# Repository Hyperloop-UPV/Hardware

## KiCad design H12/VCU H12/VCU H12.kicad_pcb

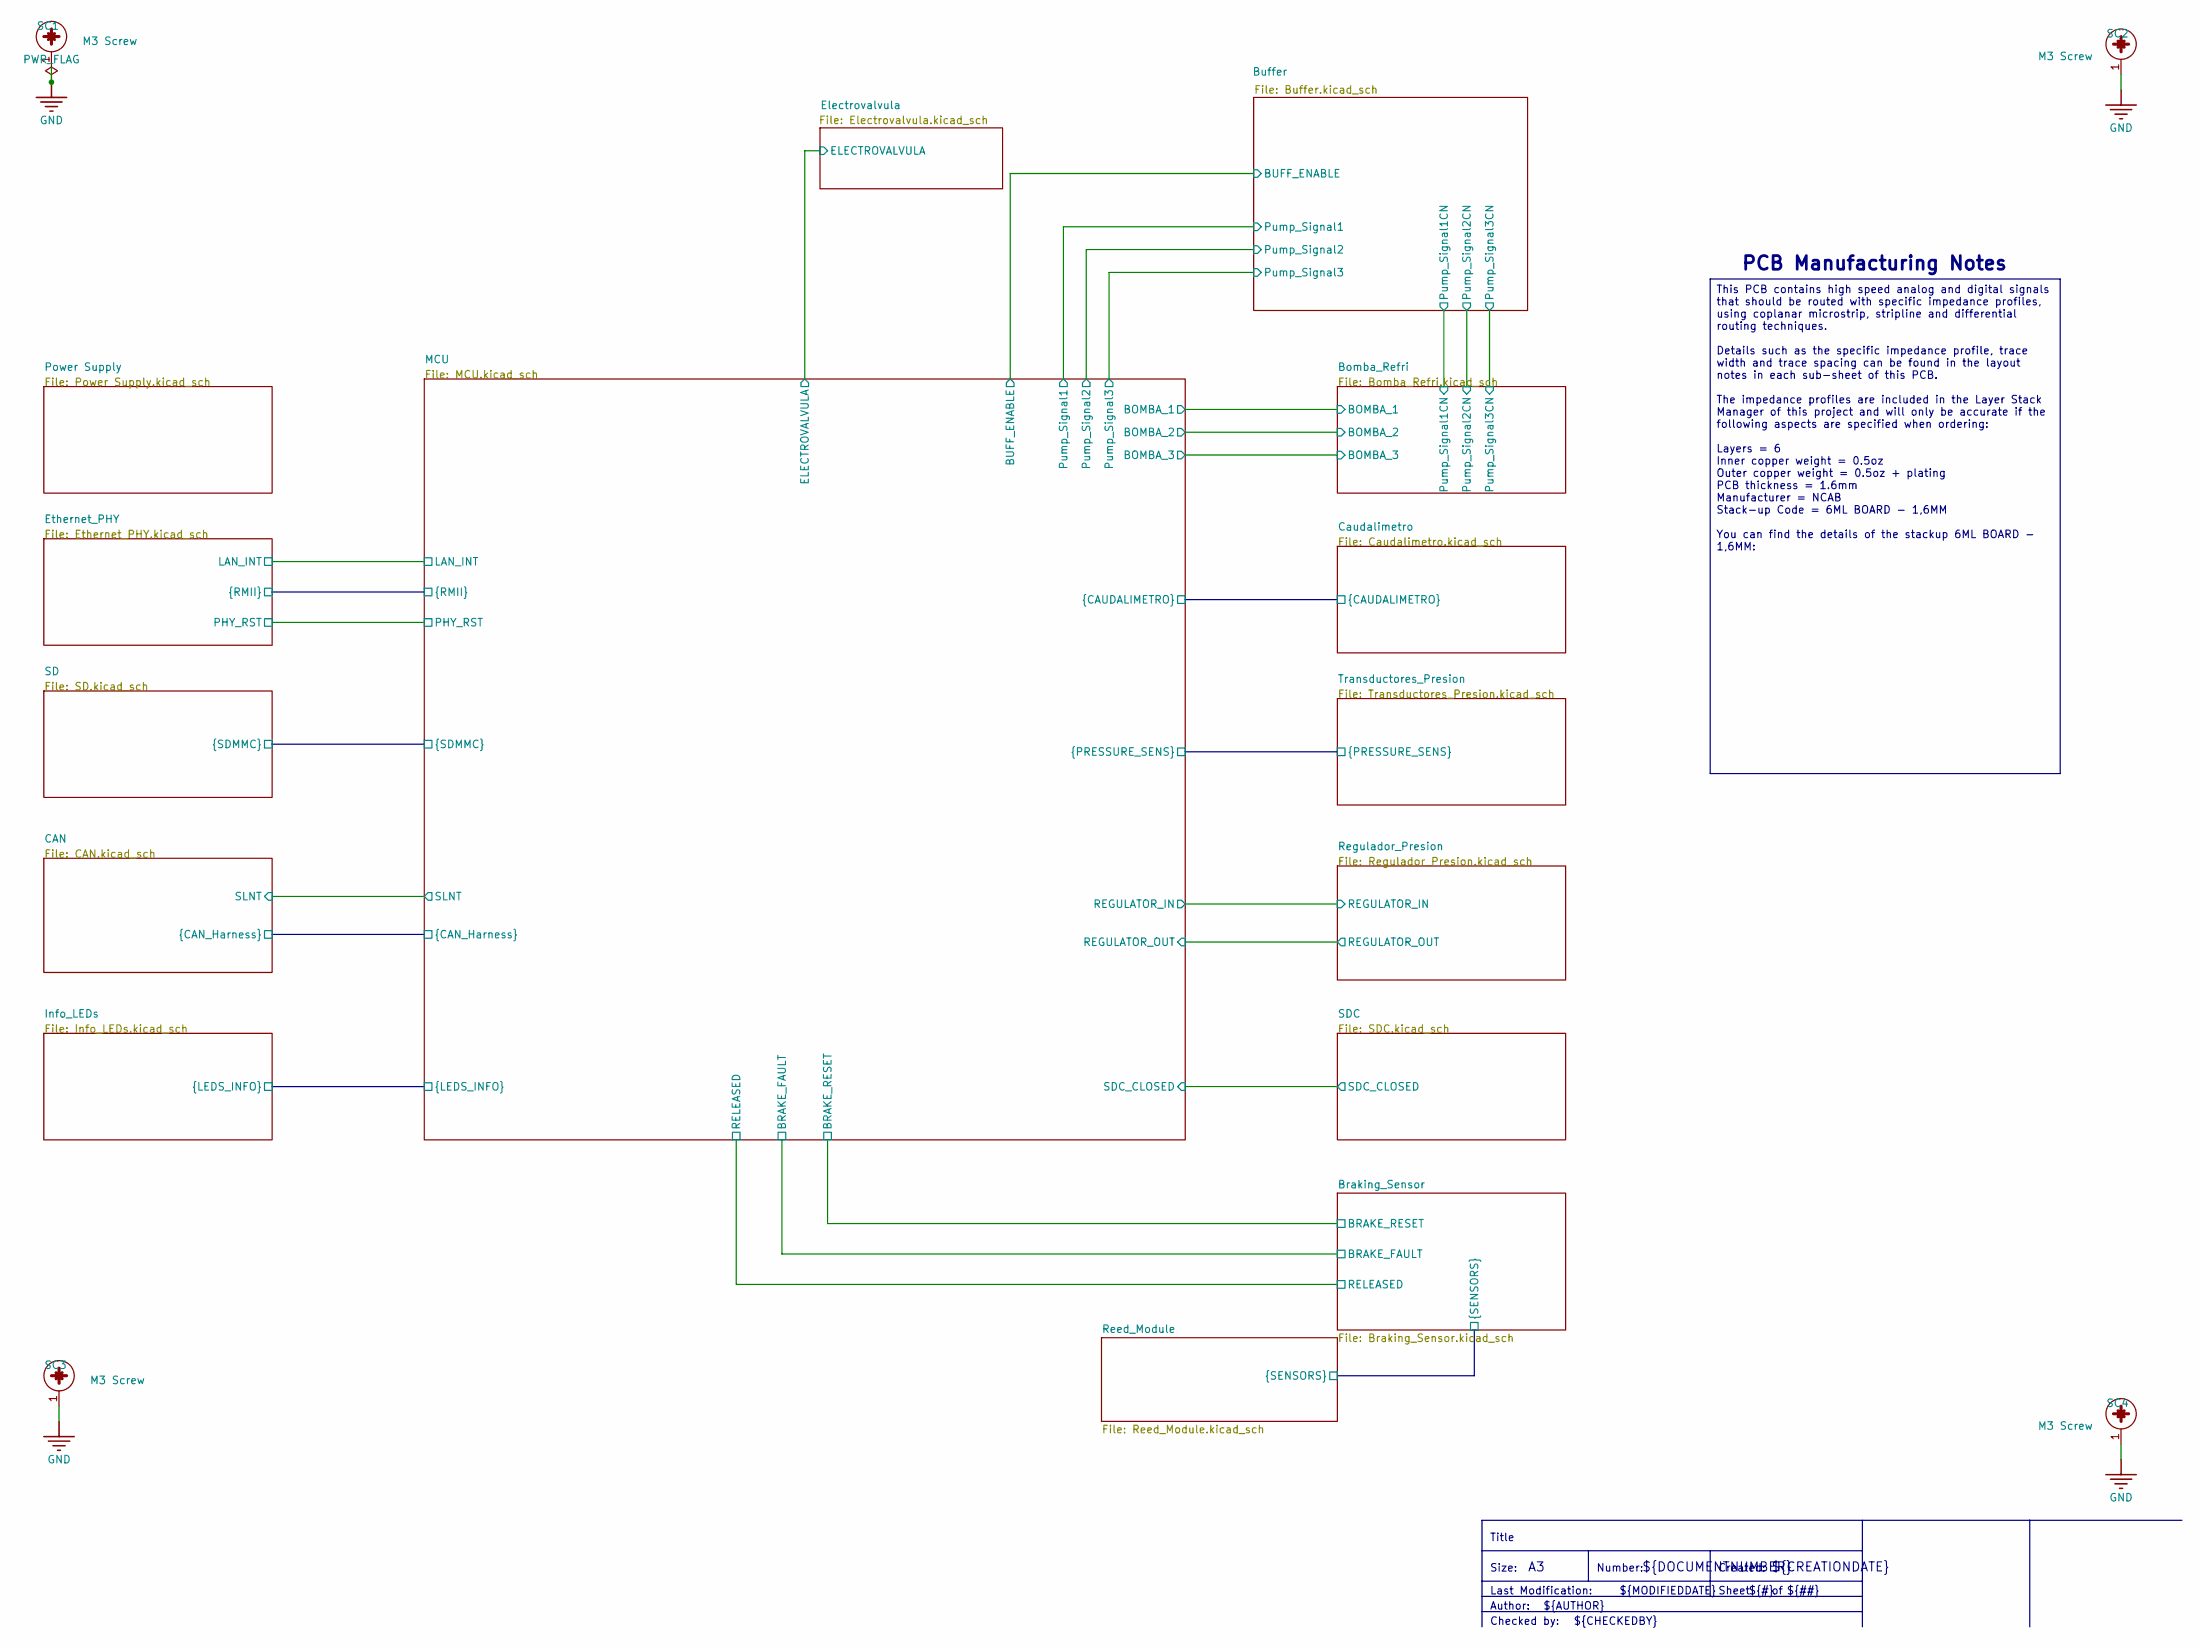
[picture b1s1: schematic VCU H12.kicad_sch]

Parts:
SC1, SC2, SC3, SC4: M3 Screw; M3 Screw-Footprint-1

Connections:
GND: SC1.1 (1_1), SC2.1 (1_1), SC3.1 (1_1), SC4.1 (1_1); also elsewhere on the board

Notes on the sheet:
PCB Manufacturing Notes
${CREATIONDATE}
${DOCUMENTNUMBER}
Size:
Sheet
Title
Number:
Author:
Last Modification:
${##}
Created:
${TITLE}
Checked by:
${MODIFIEDDATE}
${#}
${CHECKEDBY}
${AUTHOR}
This PCB contains high speed analog and digital signals that should be routed with specific impedance profiles, using coplanar microstrip, stripline and differential routing techniques. Details such as the specific impedance profile, trace width and trace spacing can be found in the layout notes in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

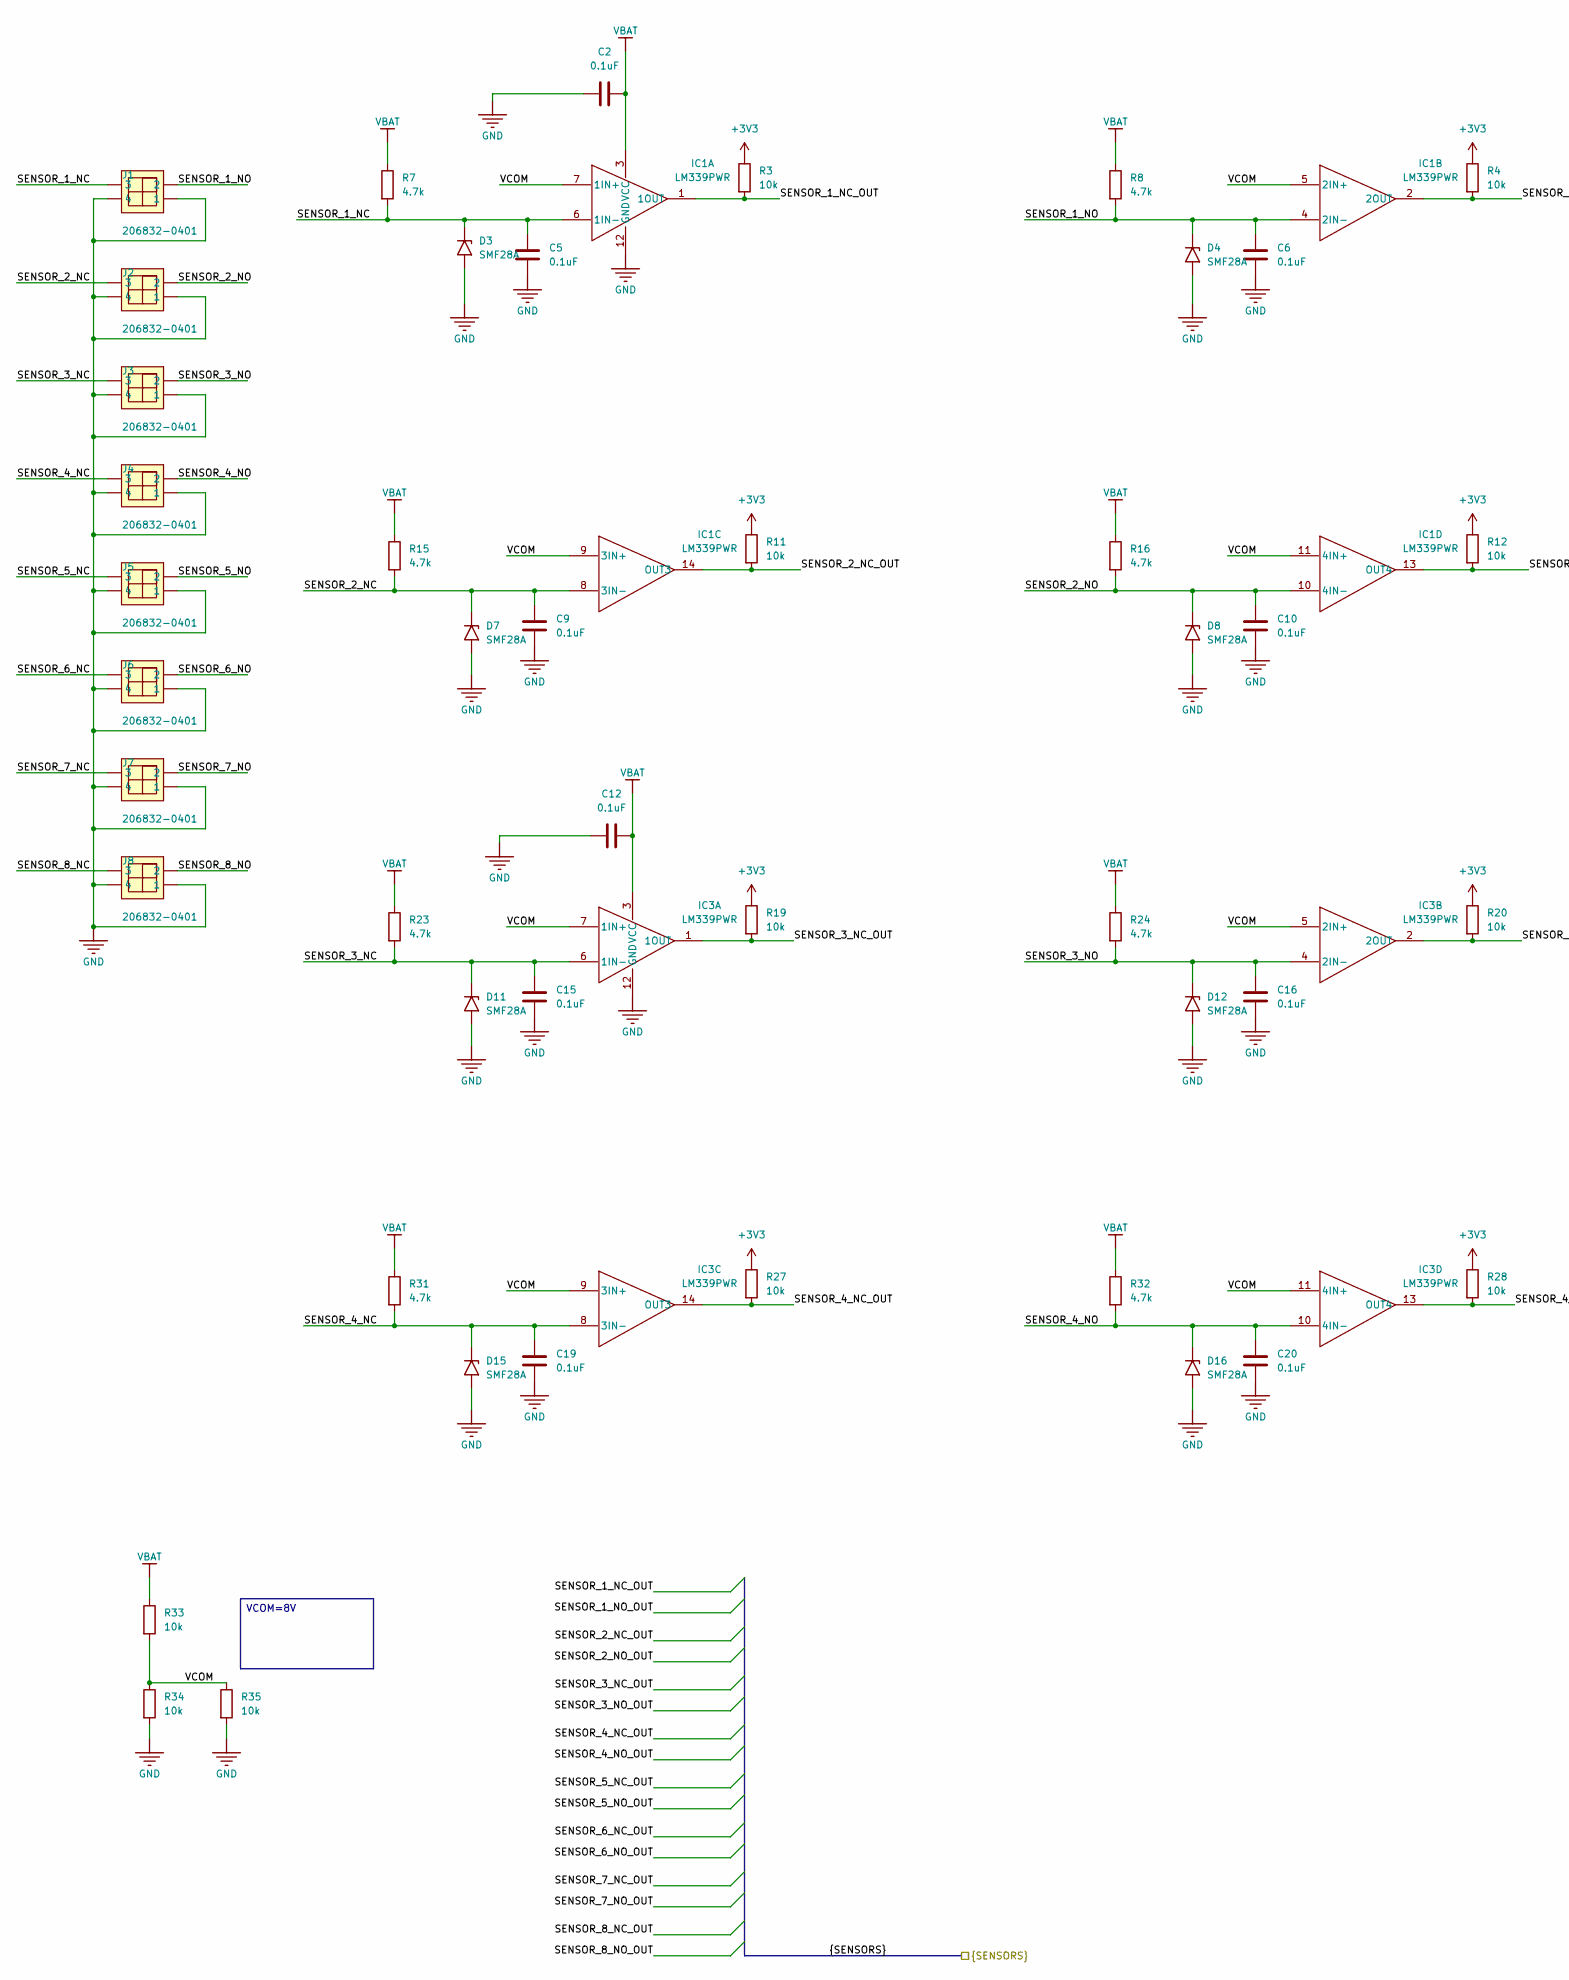
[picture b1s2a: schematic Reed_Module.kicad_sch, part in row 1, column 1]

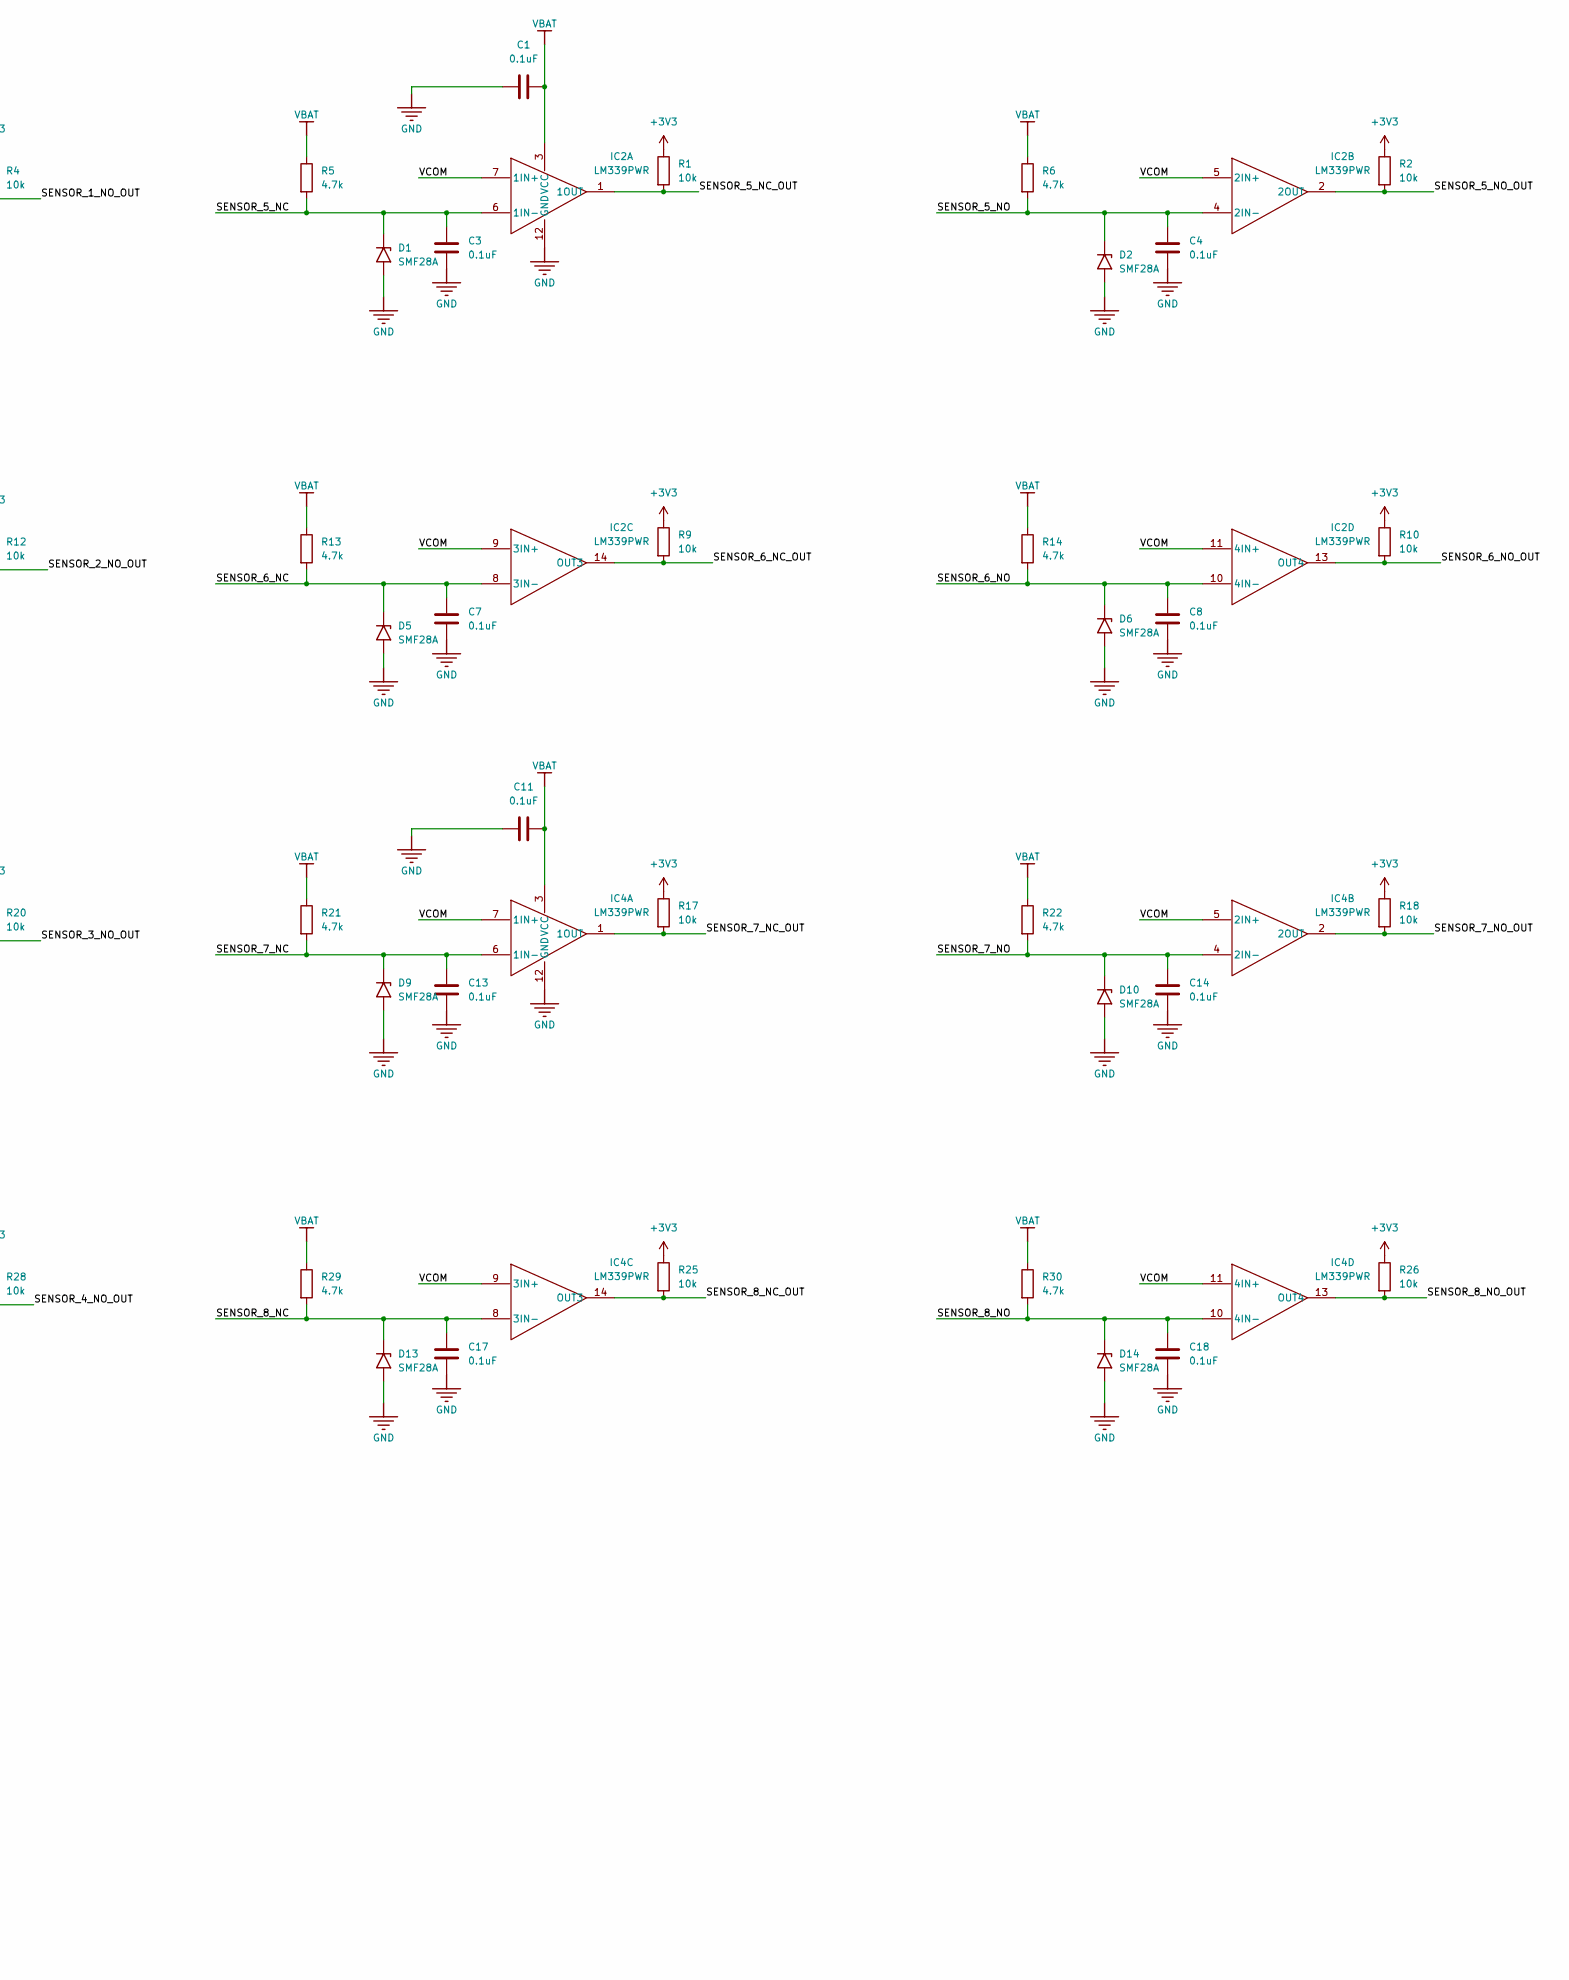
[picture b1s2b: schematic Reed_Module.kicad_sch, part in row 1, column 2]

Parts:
C1, C2, C3, C4, C5, C6, C7, C8, C9, C10, C11, C12, C13, C14, C15, C16, C17, C18, C19, C20: 0.1uF; CAP 0603_1608
D1, D2, D3, D4, D5, D6, D7, D8, D9, D10, D11, D12, D13, D14, D15, D16: SMF28A; D_SMF
IC1, IC2, IC3, IC4: LM339PWR; SOP65P640X120-14N; Manufacturer_Part_Number LM339PWR; Mouser Part Number 595-LM339PWR
J1, J2, J3, J4, J5, J6, J7, J8: 206832-0401; 206832-0401-Footprint-1; MAX VOLTAGE 600V AC (RMS)/DC
R1, R2, R3, R4, R9, R10, R11, R12, R17, R18, R19, R20, R25, R26, R27, R28, R33, R34, R35: 10k; RES 0603_1608
R5, R6, R7, R8, R13, R14, R15, R16, R21, R22, R23, R24, R29, R30, R31, R32: 4.7k; RES 0603_1608

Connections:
+3V3: R1.1, R2.1, R3.1, R4.1, R9.1, R10.1, R11.1, R12.1, R17.1, R18.1, R19.1, R20.1, R25.1, R26.1, R27.1, R28.1; also elsewhere on the board
/Braking_Sensor/SENSOR_1_NC_OUT: IC1.1 (1OUT), R3.2; also elsewhere on the board
/Braking_Sensor/SENSOR_1_NO_OUT: IC1.2 (2OUT), R4.2; also elsewhere on the board
/Braking_Sensor/SENSOR_2_NC_OUT: IC1.14 (OUT3), R11.2; also elsewhere on the board
/Braking_Sensor/SENSOR_2_NO_OUT: IC1.13 (OUT4), R12.2; also elsewhere on the board
/Braking_Sensor/SENSOR_3_NC_OUT: IC3.1 (1OUT), R19.2; also elsewhere on the board
/Braking_Sensor/SENSOR_3_NO_OUT: IC3.2 (2OUT), R20.2; also elsewhere on the board
/Braking_Sensor/SENSOR_4_NC_OUT: IC3.14 (OUT3), R27.2; also elsewhere on the board
/Braking_Sensor/SENSOR_4_NO_OUT: IC3.13 (OUT4), R28.2; also elsewhere on the board
/Braking_Sensor/SENSOR_5_NC_OUT: IC2.1 (1OUT), R1.2; also elsewhere on the board
/Braking_Sensor/SENSOR_5_NO_OUT: IC2.2 (2OUT), R2.2; also elsewhere on the board
/Braking_Sensor/SENSOR_6_NC_OUT: IC2.14 (OUT3), R9.2; also elsewhere on the board
/Braking_Sensor/SENSOR_6_NO_OUT: IC2.13 (OUT4), R10.2; also elsewhere on the board
/Braking_Sensor/SENSOR_7_NC_OUT: IC4.1 (1OUT), R17.2; also elsewhere on the board
/Braking_Sensor/SENSOR_7_NO_OUT: IC4.2 (2OUT), R18.2; also elsewhere on the board
/Braking_Sensor/SENSOR_8_NC_OUT: IC4.14 (OUT3), R25.2; also elsewhere on the board
/Braking_Sensor/SENSOR_8_NO_OUT: IC4.13 (OUT4), R26.2; also elsewhere on the board
/Reed_Module/SENSOR_1_NC: C5.2, D3.1 (A1), IC1.6 (1IN-), J1.3, R7.2
/Reed_Module/SENSOR_1_NO: C6.2, D4.1 (A1), IC1.4 (2IN-), J1.2, R8.2
/Reed_Module/SENSOR_2_NC: C9.2, D7.1 (A1), IC1.8 (3IN-), J2.3, R15.2
/Reed_Module/SENSOR_2_NO: C10.2, D8.1 (A1), IC1.10 (4IN-), J2.2, R16.2
/Reed_Module/SENSOR_3_NC: C15.2, D11.1 (A1), IC3.6 (1IN-), J3.3, R23.2
/Reed_Module/SENSOR_3_NO: C16.2, D12.1 (A1), IC3.4 (2IN-), J3.2, R24.2
/Reed_Module/SENSOR_4_NC: C19.2, D15.1 (A1), IC3.8 (3IN-), J4.3, R31.2
/Reed_Module/SENSOR_4_NO: C20.2, D16.1 (A1), IC3.10 (4IN-), J4.2, R32.2
/Reed_Module/SENSOR_5_NC: C3.2, D1.1 (A1), IC2.6 (1IN-), J5.3, R5.2
/Reed_Module/SENSOR_5_NO: C4.2, D2.1 (A1), IC2.4 (2IN-), J5.2, R6.2
/Reed_Module/SENSOR_6_NC: C7.2, D5.1 (A1), IC2.8 (3IN-), J6.3, R13.2
/Reed_Module/SENSOR_6_NO: C8.2, D6.1 (A1), IC2.10 (4IN-), J6.2, R14.2
/Reed_Module/SENSOR_7_NC: C13.2, D9.1 (A1), IC4.6 (1IN-), J7.3, R21.2
/Reed_Module/SENSOR_7_NO: C14.2, D10.1 (A1), IC4.4 (2IN-), J7.2, R22.2
/Reed_Module/SENSOR_8_NC: C17.2, D13.1 (A1), IC4.8 (3IN-), J8.3, R29.2
/Reed_Module/SENSOR_8_NO: C18.2, D14.1 (A1), IC4.10 (4IN-), J8.2, R30.2
/Reed_Module/VCOM: IC1.5 (2IN+), IC1.7 (1IN+), IC1.9 (3IN+), IC1.11 (4IN+), IC2.5 (2IN+), IC2.7 (1IN+), IC2.9 (3IN+), IC2.11 (4IN+), IC3.5 (2IN+), IC3.7 (1IN+), IC3.9 (3IN+), IC3.11 (4IN+), IC4.5 (2IN+), IC4.7 (1IN+), IC4.9 (3IN+), IC4.11 (4IN+), R33.2, R34.1, R35.1
GND: C1.1, C2.1, C3.1, C4.1, C5.1, C6.1, C7.1, C8.1, C9.1, C10.1, C11.1, C12.1, C13.1, C14.1, C15.1, C16.1, C17.1, C18.1, C19.1, C20.1, D1.2 (A2), D2.2 (A2), D3.2 (A2), D4.2 (A2), D5.2 (A2), D6.2 (A2), D7.2 (A2), D8.2 (A2), D9.2 (A2), D10.2 (A2), D11.2 (A2), D12.2 (A2), D13.2 (A2), D14.2 (A2), D15.2 (A2), D16.2 (A2), IC1.12 (GND), IC2.12 (GND), IC3.12 (GND), IC4.12 (GND), J1.1, J1.4, J2.1, J2.4, J3.1, J3.4, J4.1, J4.4, J5.1, J5.4, J6.1, J6.4, J7.1, J7.4, J8.1, J8.4, R34.2, R35.2; also elsewhere on the board
VBAT: C1.2, C2.2, C11.2, C12.2, IC1.3 (VCC), IC2.3 (VCC), IC3.3 (VCC), IC4.3 (VCC), R5.1, R6.1, R7.1, R8.1, R13.1, R14.1, R15.1, R16.1, R21.1, R22.1, R23.1, R24.1, R29.1, R30.1, R31.1, R32.1, R33.1; also elsewhere on the board

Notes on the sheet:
VCOM=8V

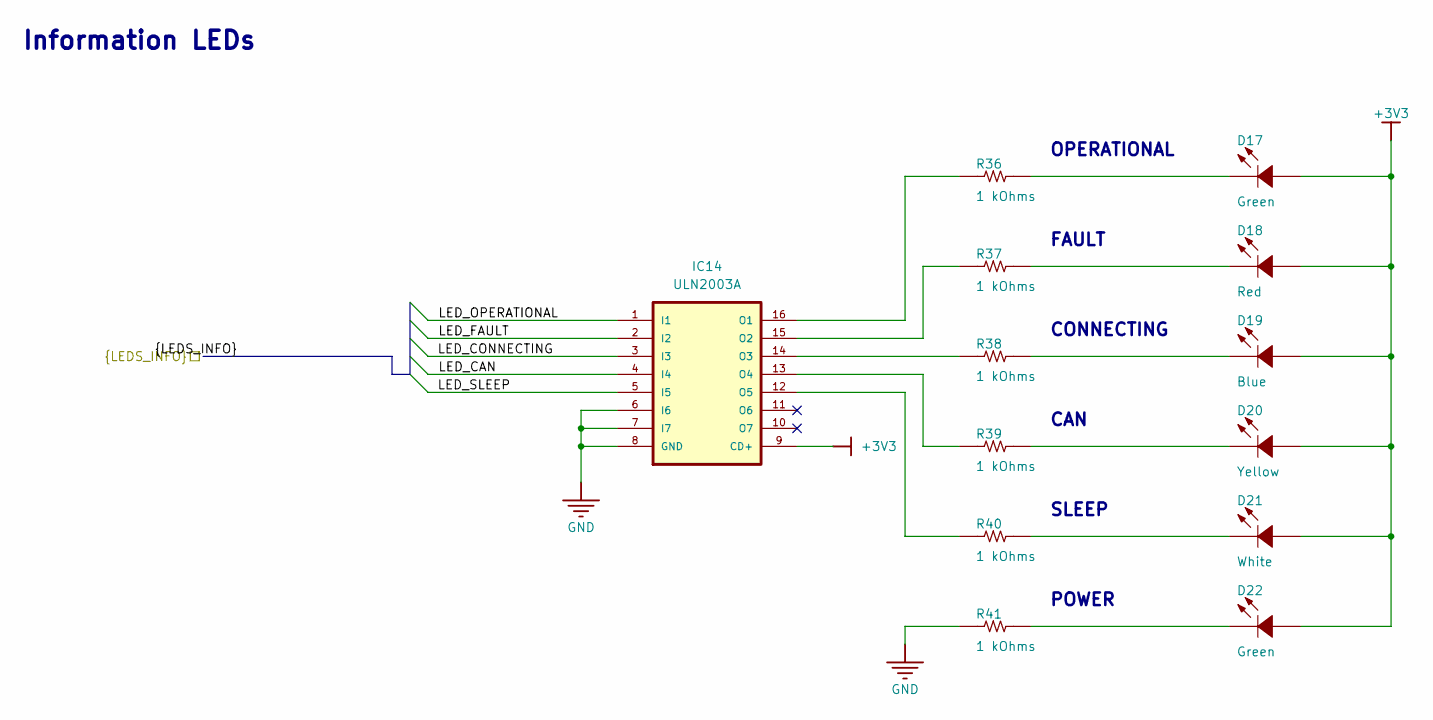
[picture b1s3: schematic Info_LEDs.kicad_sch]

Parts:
D17, D22: Green; LED 0603_1608 GREEN; MILLICANDELA RATING 260.5mcd; VOLTAGE - FORWARD (VF) 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 3.2V; PART NUMBER VLMTG1300-GS08
D18: Red; LED 0603_1608 RED; MILLICANDELA RATING 54mcd; VOLTAGE - FORWARD (VF) 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 2V; PART NUMBER VLMS1300-GS08
D19: Blue; LED 0603_1608 BLUE; MILLICANDELA RATING 104mcd; VOLTAGE - FORWARD (VF) 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 3.3V; PART NUMBER VLMB1310-GS08
D20: Yellow; LED 0603_1608 YELLOW; MILLICANDELA RATING 63mcd; VOLTAGE - FORWARD (VF) 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 2.2V; PART NUMBER SML-D12Y8WT86
D21: White; LED 0603_1608; MILLICANDELA RATING 300mcd; VOLTAGE - FORWARD (VF) 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 2.9V; PART NUMBER CL-198N-WS-D-T
IC14: ULN2003A; ULN2003AD; MPN ULN2003A
R36, R37, R38, R39, R40, R41: 1 kOhms; RES 0603_1608; RATINGS AEC-Q200; TOLERANCE ±0.1%; PART NUMBER RNCS0603BKE10K0

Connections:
+3V3: D17.1, D18.1, D19.1, D20.1, D21.1, D22.1, IC14.9 (CD+); also elsewhere on the board
/Info_LEDs/LED_CAN: IC14.4 (I4); also elsewhere on the board
/Info_LEDs/LED_CONNECTING: IC14.3 (I3); also elsewhere on the board
/Info_LEDs/LED_FAULT: IC14.2 (I2); also elsewhere on the board
/Info_LEDs/LED_OPERATIONAL: IC14.1 (I1); also elsewhere on the board
/Info_LEDs/LED_SLEEP: IC14.5 (I5); also elsewhere on the board
GND: IC14.6 (I6), IC14.7 (I7), IC14.8 (GND), R41.1; also elsewhere on the board
unnamed: D17.2, R36.2
unnamed: D18.2, R37.2
unnamed: D19.2, R38.2
unnamed: D20.2, R39.2
unnamed: D21.2, R40.2
unnamed: D22.2, R41.2
unnamed: IC14.16 (O1), R36.1
unnamed: IC14.15 (O2), R37.1
unnamed: IC14.14 (O3), R38.1
unnamed: IC14.13 (O4), R39.1
unnamed: IC14.12 (O5), R40.1

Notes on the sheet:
OPERATIONAL
POWER
FAULT
CAN
SLEEP
Information LEDs
CONNECTING

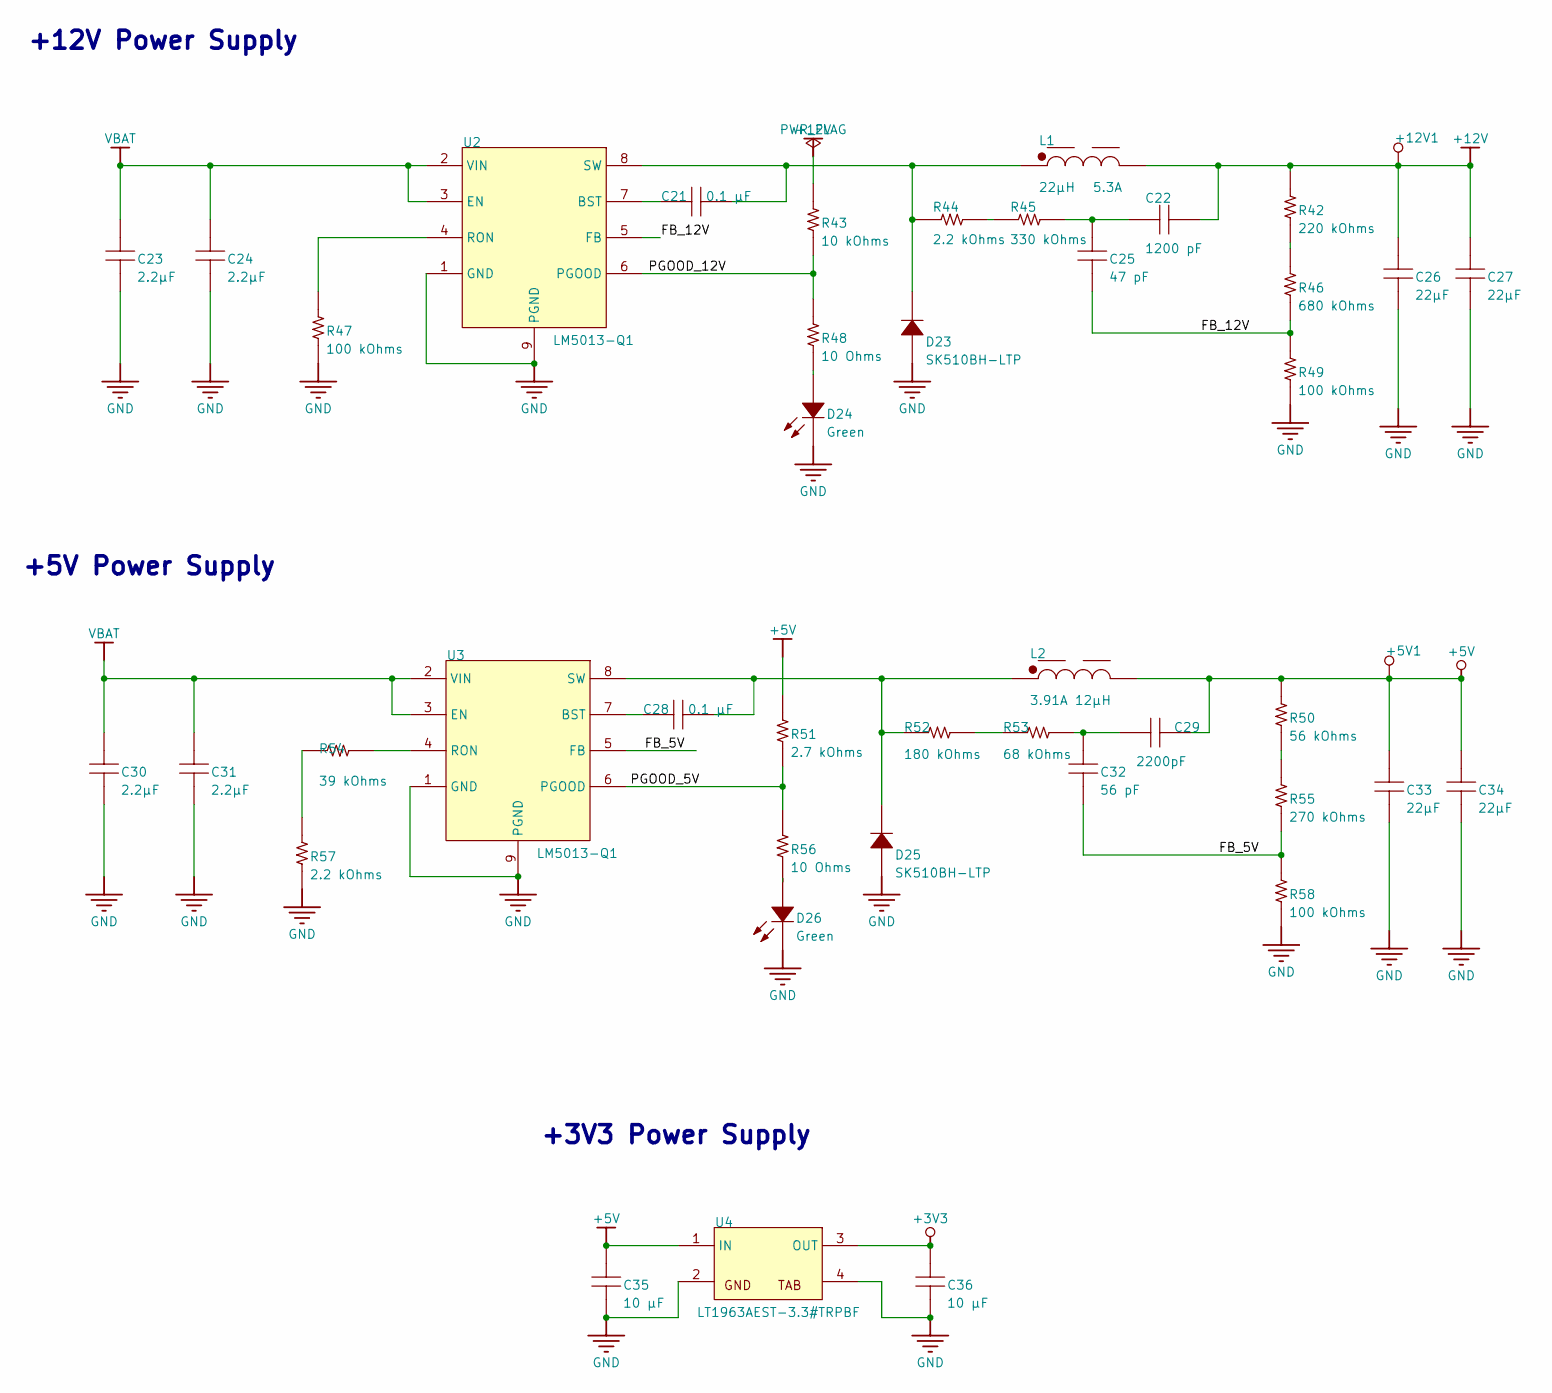
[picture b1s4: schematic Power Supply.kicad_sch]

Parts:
+5V1, +12V1: Test point 1.2mm; Test point 1.2mm-Footprint-1
C21, C28: 0.1 µF; CAP 0603_1608; TOLERANCE ±10%; VOLTAGE - RATED 100V; PART NUMBER C0603X104K101T
C22: 1200 pF; CAP 0603_1608; TOLERANCE ±10%; VOLTAGE - RATED 100V; PART NUMBER C0603C122K1RAC7867
C23, C24, C30, C31: 2.2µF; CAP 1206_3216 - 1.8MM; TOLERANCE ±10%; VOLTAGE - RATED 100V; PART NUMBER 12061C225KAT4A
C25: 47 pF; MURATA GQM187 0603_1608; TOLERANCE ±5%; VOLTAGE - RATED 250V; PART NUMBER GQM1875C2E560JB12D
C26, C27, C33, C34: 22µF; CAP 1206_3216 - 1.8MM; TOLERANCE ±10%; VOLTAGE - RATED 25V; PART NUMBER 12063D226KAT2A
C29: 2200pF; CAP 0603_1608; TOLERANCE ±5%; VOLTAGE - RATED 50V; PART NUMBER 06035A222JAT2A
C32: 56 pF; MURATA GQM187 0603_1608; TOLERANCE ±5%; VOLTAGE - RATED 250V; PART NUMBER GQM1875C2E560JB12D
C35, C36: 10 µF; CAP 1206_3216 - 0.8MM; RATINGS AEC-Q200; TOLERANCE ±5%; PART NUMBER C1206X106J3RACAUTO
D23, D25: SK510BH-LTP; DO214AA SMB; VOLTAGE - DC REVERSE (V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 100V; VOLTAGE - FORWARD (VF) 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 850mV @ 5A; PART NUMBER SK510BH-LTP
D24, D26: Green; LED 0603_1608 GREEN; MILLICANDELA RATING 260.5mcd; VOLTAGE - FORWARD (VF) 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 3.2V; PART NUMBER VLMTG1300-GS08
L1: 7447709220; WE-PD_1210; MANUFACTURER PART NUMBER 7447709220
L2: 744771112; WE-PD_1260; MANUFACTURER PART NUMBER 744771112
R42: 220 kOhms; RES 0603_1608; RATINGS AEC-Q200; TOLERANCE ±1%; PART NUMBER CRCW0603909KFKEA
R43: 10 kOhms; YAGEO RES 0603_1608; TOLERANCE ±1%; PART NUMBER RT0603FRE0710KL
R44: 2.2 kOhms; KOA RES RK73 RN73 0603_1608; RATINGS AEC-Q200; TOLERANCE ±1%; PART NUMBER RK73H1JTTD3323F
R45: 330 kOhms; KOA RES RK73 RN73 0603_1608; RATINGS AEC-Q200; TOLERANCE ±1%; PART NUMBER RK73H1JTTD3323F
R46: 680 kOhms; RES 0603_1608; RATINGS AEC-Q200; TOLERANCE ±1%; PART NUMBER CRCW0603909KFKEA
R47, R49, R58: 100 kOhms; RES 0603_1608; RATINGS AEC-Q200; TOLERANCE ±0.1%; PART NUMBER RNCS0603BKE100K
R48, R56: 10 Ohms; YAGEO RES 0603_1608; TOLERANCE ±1%; PART NUMBER RT0603FRE0710KL
R50: 56 kOhms; RES 0603_1608; RATINGS AEC-Q200; TOLERANCE ±1%; PART NUMBER CRCW0603316KFKEA
R51: 2.7 kOhms; YAGEO RES 0603_1608; TOLERANCE ±1%; PART NUMBER RT0603FRE0710KL
R52: 180 kOhms; RES 0603_1608; RATINGS AEC-Q200; TOLERANCE ±0.1%; PART NUMBER ERA-3AEB2493V
R53: 68 kOhms; RES 0603_1608; RATINGS AEC-Q200; TOLERANCE ±0.1%; PART NUMBER ERA-3AEB2493V
R54: 39 kOhms; RES 0603_1608; TOLERANCE ±1%; PART NUMBER CR0603-FX-4122ELF
R55: 270 kOhms; RES 0603_1608; RATINGS AEC-Q200; TOLERANCE ±1%; PART NUMBER CRCW0603316KFKEA
R57: 2.2 kOhms; RES 0603_1608; TOLERANCE ±1%; PART NUMBER CR0603-FX-4122ELF
U2, U3: LM5013-Q1; SOIC127P600X170_HS-9N
U4: LT1963AEST-3.3#TRPBF; SOT230P700X180-4N

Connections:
+3V3: C36.2, U4.3 (OUT); also elsewhere on the board
+5V: +5V1.1 (*_1), C29.2, C33.2, C34.2, C35.2, L2.2, R50.2, R51.2, U4.1 (IN); also elsewhere on the board
+12V: +12V1.1 (*_1), C22.2, C26.2, C27.2, L1.2, R42.2, R43.2; also elsewhere on the board
/Power Supply/FB_5V: C32.1, R55.1, R58.2, U3.5 (FB)
/Power Supply/FB_12V: C25.1, R46.1, R49.2, U2.5 (FB)
/Power Supply/PGOOD_5V: R51.1, R56.2, U3.6 (PGOOD)
/Power Supply/PGOOD_12V: R43.1, R48.2, U2.6 (PGOOD)
GND: C23.1, C24.1, C26.1, C27.1, C30.1, C31.1, C33.1, C34.1, C35.1, C36.1, D23.1, D24.2, D25.1, D26.2, R47.1, R49.1, R57.1, R58.1, U2.1 (GND), U2.9 (PGND), U3.1 (GND), U3.9 (PGND), U4.2 (GND), U4.4 (TAB); also elsewhere on the board
unnamed: C22.1, C25.2, R45.2
unnamed: C29.1, C32.2, R53.2
unnamed: D24.1, R48.1
unnamed: D26.1, R56.1
unnamed: R42.1, R46.2
unnamed: R44.2, R45.1
unnamed: R50.1, R55.2
unnamed: R52.2, R53.1
unnamed: R54.2, R57.2
unnamed: C21.1, U2.7 (BST)
unnamed: R47.2, U2.4 (RON)
unnamed: C21.2, D23.2, L1.1, R44.1, U2.8 (SW)
unnamed: C28.1, U3.7 (BST)
unnamed: R54.1, U3.4 (RON)
unnamed: C28.2, D25.2, L2.1, R52.1, U3.8 (SW)
VBAT: C23.2, C24.2, C30.2, C31.2, U2.2 (VIN), U2.3 (EN), U3.2 (VIN), U3.3 (EN); also elsewhere on the board

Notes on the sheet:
+3V3 Power Supply
+12V Power Supply
+5V Power Supply

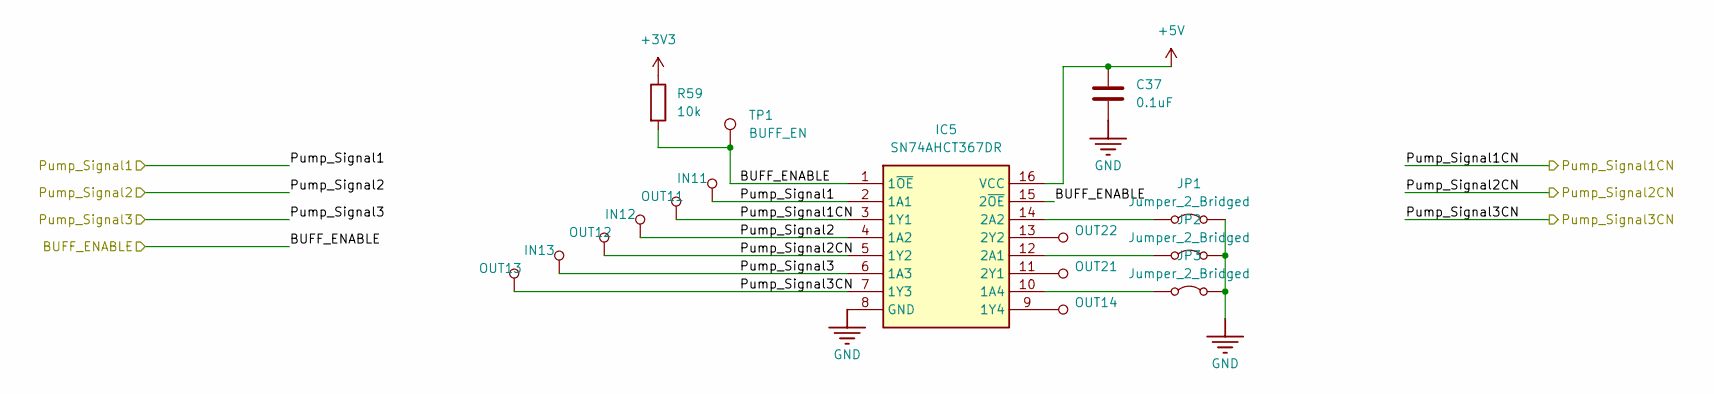
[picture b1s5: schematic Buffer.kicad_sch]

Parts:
C37: 0.1uF; CAP 0603_1608
IC5: SN74AHCT367DR; SOIC127P600X175-16N; Manufacturer_Part_Number SN74AHCT367DR; Mouser Part Number 595-SN74AHCT367DR
IN11, IN12, IN13: Test point 1.2mm; Test point 1.2mm-Footprint-1
JP1, JP2, JP3: Jumper_2_Bridged; SolderJumper-2_P1.3mm_Bridged_Pad1.0x1.5mm
OUT11, OUT12, OUT13, OUT14, OUT21, OUT22: Test point 1.2mm; Test point 1.2mm-Footprint-1
R59: 10k; R_0603_1608Metric
TP1: BUFF_EN; Test point 1.2mm-Footprint-1

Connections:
+3V3: R59.1; also elsewhere on the board
+5V: C37.1, IC5.16 (VCC); also elsewhere on the board
/Buffer/BUFF_ENABLE: IC5.1 (1~OE), IC5.15 (2~OE), R59.2, TP1.1 (1_1); also elsewhere on the board
/Buffer/Pump_Signal1: IC5.2 (1A1), IN11.1 (*_1); also elsewhere on the board
/Buffer/Pump_Signal1CN: IC5.3 (1Y1), OUT11.1 (*_1); also elsewhere on the board
/Buffer/Pump_Signal2: IC5.4 (1A2), IN12.1 (*_1); also elsewhere on the board
/Buffer/Pump_Signal2CN: IC5.5 (1Y2), OUT12.1 (*_1); also elsewhere on the board
/Buffer/Pump_Signal3: IC5.6 (1A3), IN13.1 (*_1); also elsewhere on the board
/Buffer/Pump_Signal3CN: IC5.7 (1Y3), OUT13.1 (*_1); also elsewhere on the board
GND: C37.2, IC5.8 (GND), JP1.2 (B), JP2.2 (B), JP3.2 (B); also elsewhere on the board
unnamed: IC5.10 (1A4), JP3.1 (A)
unnamed: IC5.9 (1Y4), OUT14.1 (*_1)
unnamed: IC5.12 (2A1), JP2.1 (A)
unnamed: IC5.14 (2A2), JP1.1 (A)
unnamed: IC5.11 (2Y1), OUT21.1 (*_1)
unnamed: IC5.13 (2Y2), OUT22.1 (*_1)

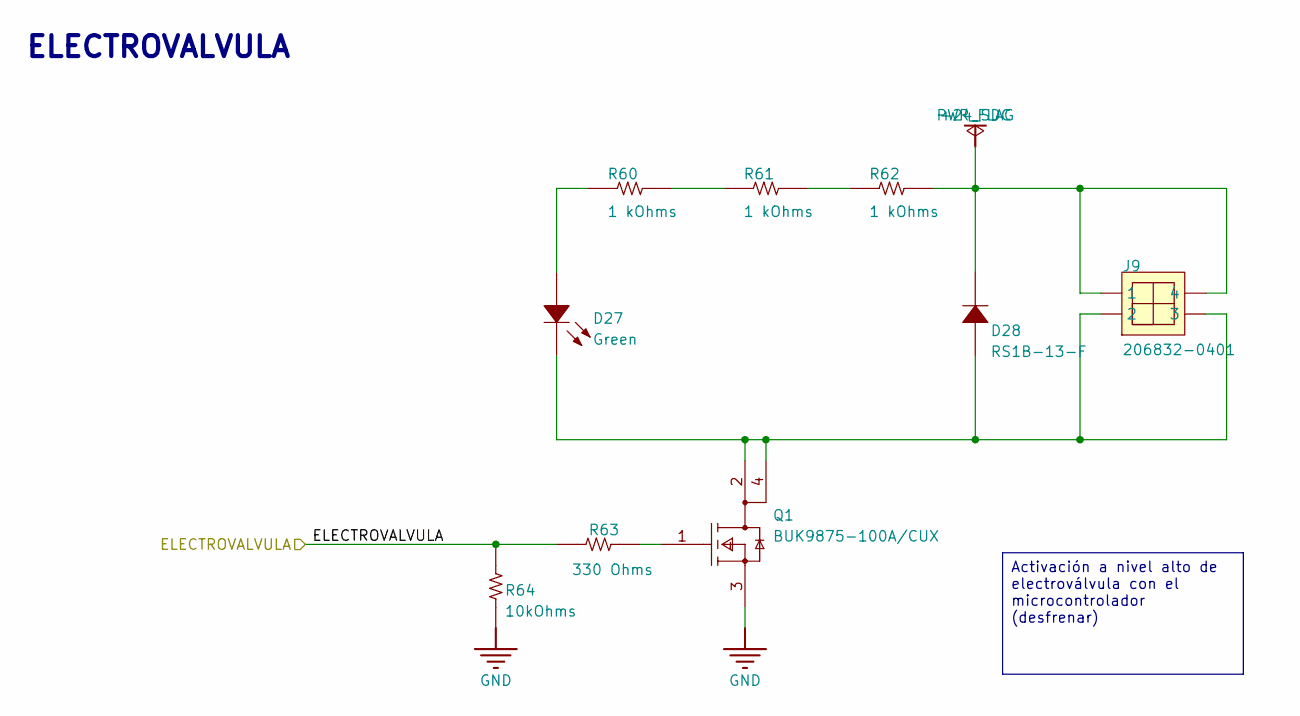
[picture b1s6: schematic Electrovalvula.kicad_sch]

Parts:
D27: Green; LED 0603_1608 GREEN; MILLICANDELA RATING 15mcd; VOLTAGE - FORWARD (VF) 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 2.1V; PART NUMBER QTLP601C4TR
D28: RS1B-13-F; DO214AC SMA; VOLTAGE - DC REVERSE (V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 100 V; VOLTAGE - FORWARD (VF) 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 1.3 V @ 1 A; PART NUMBER RS1B-13-F
J9: 206832-0401; 206832-0401-Footprint-1; MAX VOLTAGE 600V AC (RMS)/DC
Q1: BUK9875-100A/CUX; BUK9875-100A_CUX-Footprint-1
R60, R61, R62: 1 kOhms; RES 0603_1608; RATINGS AEC-Q200; TOLERANCE ±0.1%; PART NUMBER RNCS0603BKE10K0
R63: 330 Ohms; RES 0603_1608; RATINGS AEC-Q200; TOLERANCE ±1%; PART NUMBER CRGCQ0603F330R
R64: 10kOhms; RES 0603_1608; RATINGS AEC-Q200; TOLERANCE ±1%; PART NUMBER CRGCQ0603F330R

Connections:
+24_SDC: D28.2, J9.1, J9.4, R62.2; also elsewhere on the board
/Electrovalvula/ELECTROVALVULA: R63.1, R64.2; also elsewhere on the board
GND: Q1.3 (S), R64.1; also elsewhere on the board
unnamed: D27.1, R60.1
unnamed: D27.2, D28.1, J9.2, J9.3, Q1.2 (D), Q1.4 (D)
unnamed: Q1.1 (G), R63.2
unnamed: R60.2, R61.1
unnamed: R61.2, R62.1

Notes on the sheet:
ELECTROVALVULA
Activación a nivel alto de electroválvula con el microcontrolador (desfrenar)
